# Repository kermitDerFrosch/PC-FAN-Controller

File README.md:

# PC Lüfter Steuerung für 6 PWM 4-Pin Lüfter
(incl. Gerber- und Bestückungsdateien)

Der I²C und der UART Port können für die Vernetzung mehrerer Controller oder für Sensoren benutzt werden.

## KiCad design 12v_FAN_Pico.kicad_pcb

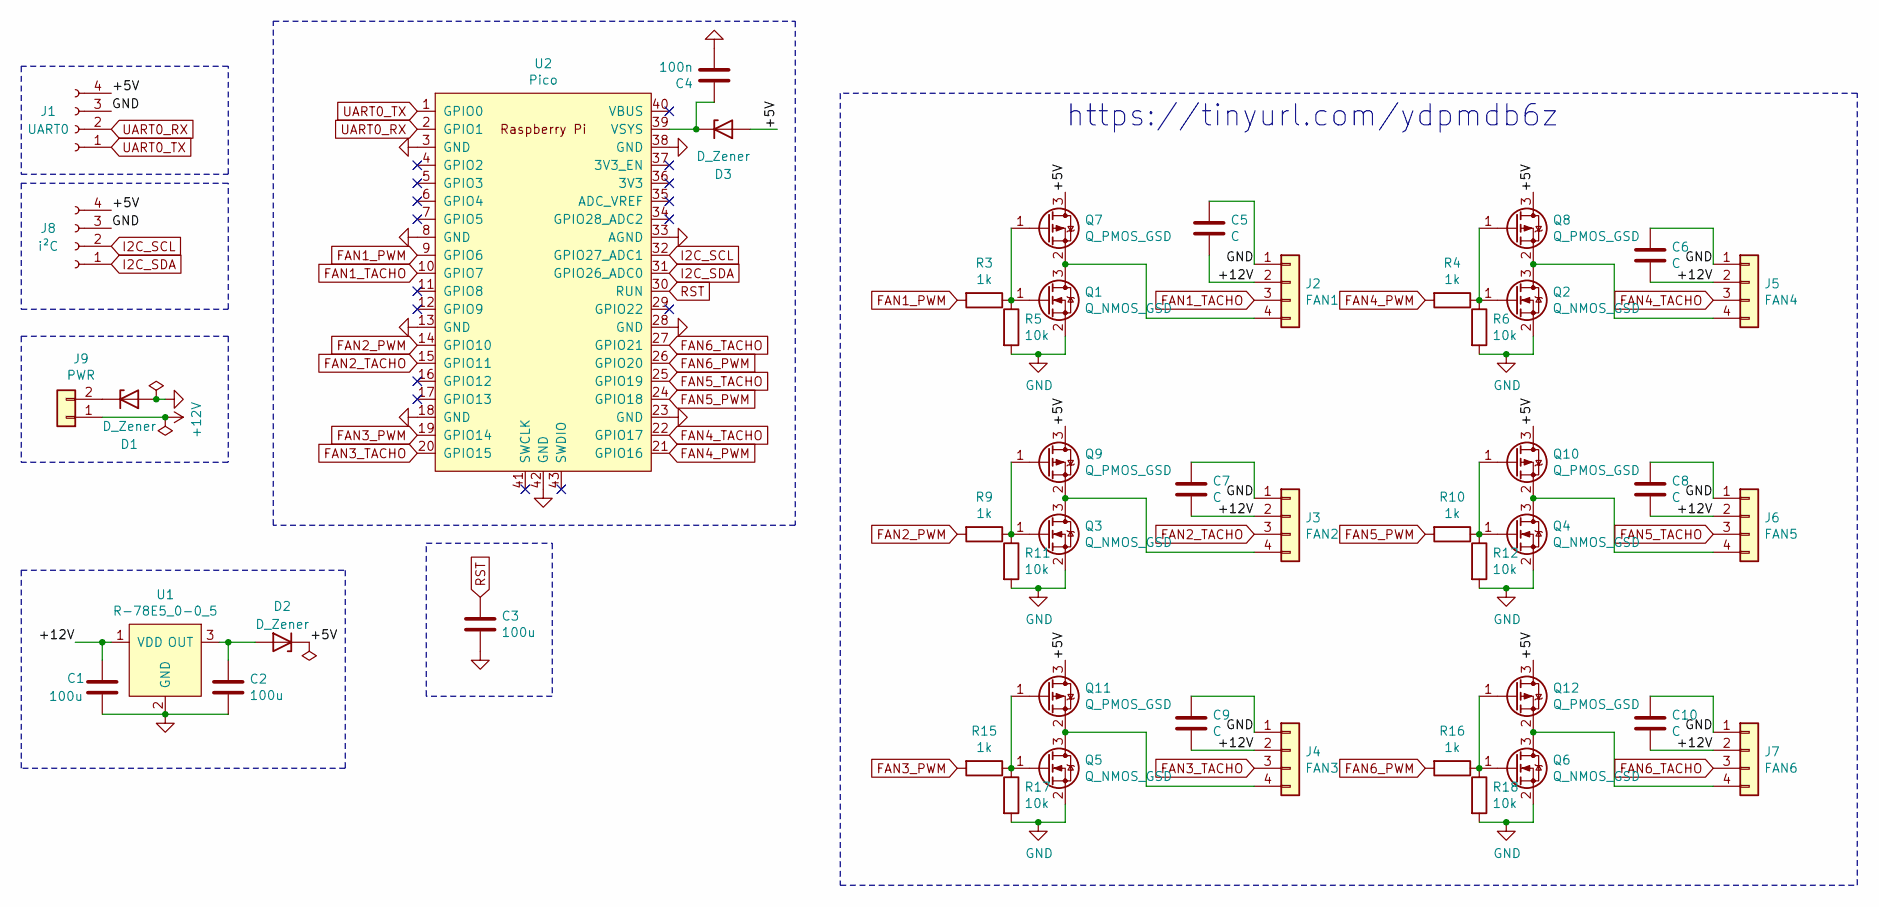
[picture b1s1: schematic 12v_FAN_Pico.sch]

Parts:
C1: 100u; CP_Radial_D6.3mm_P2.50mm
C2, C3: 100u; CP_EIA-3528-21_Kemet-B
C4: 100n; C_0402_1005Metric
C5, C6, C7, C8, C9, C10: C; C_0603_1608Metric
D1, D2, D3: D_Zener; D_A-405_P2.54mm_Vertical_AnodeUp
J1: UART0; NS-Tech_Grove_1x04_P2mm_Vertical
J2: FAN1; FanPinHeader_1x04_P2.54mm_Vertical
J3: FAN2; FanPinHeader_1x04_P2.54mm_Vertical
J4: FAN3; FanPinHeader_1x04_P2.54mm_Vertical
J5: FAN4; FanPinHeader_1x04_P2.54mm_Vertical
J6: FAN5; FanPinHeader_1x04_P2.54mm_Vertical
J7: FAN6; FanPinHeader_1x04_P2.54mm_Vertical
J8: i²C; NS-Tech_Grove_1x04_P2mm_Vertical
J9: PWR; Barrel_Jack_5.5mmODx2.1mmID_PJ-202A
Q1, Q2, Q3, Q4, Q5, Q6: Q_NMOS_GSD; SOT-23
Q7, Q8, Q9, Q10, Q11, Q12: Q_PMOS_GSD; SOT-23
R3, R4, R9, R10, R15, R16: 1k; R_0603_1608Metric
R5, R6, R11, R12, R17, R18: 10k; R_0603_1608Metric
U1: R-78E5_0-0_5; SIP-3_P2.54mm; MPN R-78E5.0-0.5; Digi-Key_PN 945-1648-5-ND
U2: Pico; RPi_Pico_SMD_TH

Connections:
+12V: C1.1, C5.2, C6.2, C7.2, C8.2, C9.2, C10.2, J2.2, J3.2, J4.2, J5.2, J6.2, J7.2, J9.1, U1.1 (VDD)
/+5V: D2.1 (K), D3.2 (A), J1.4, J8.4, Q7.3 (D), Q8.3 (D), Q9.3 (D), Q10.3 (D), Q11.3 (D), Q12.3 (D)
FAN1_PWM: R3.2, U2.9 (GPIO6)
FAN1_TACHO: J2.3, U2.10 (GPIO7)
FAN2_PWM: R9.2, U2.14 (GPIO10)
FAN2_TACHO: J3.3, U2.15 (GPIO11)
FAN3_PWM: R15.2, U2.19 (GPIO14)
FAN3_TACHO: J4.3, U2.20 (GPIO15)
FAN4_PWM: R4.2, U2.21 (GPIO16)
FAN4_TACHO: J5.3, U2.22 (GPIO17)
FAN5_PWM: R10.2, U2.24 (GPIO18)
FAN5_TACHO: J6.3, U2.25 (GPIO19)
FAN6_PWM: R16.2, U2.26 (GPIO20)
FAN6_TACHO: J7.3, U2.27 (GPIO21)
GND: C1.2, C2.2, C3.2, C4.2, C5.1, C6.1, C7.1, C8.1, C9.1, C10.1, D1.2 (A), J1.3, J2.1, J3.1, J4.1, J5.1, J6.1, J7.1, J8.3, Q1.2 (S), Q2.2 (S), Q3.2 (S), Q4.2 (S), Q5.2 (S), Q6.2 (S), R5.2, R6.2, R11.2, R12.2, R17.2, R18.2, U1.2 (GND), U2.3 (GND), U2.8 (GND), U2.13 (GND), U2.18 (GND), U2.23 (GND), U2.28 (GND), U2.33 (AGND), U2.38 (GND), U2.42 (GND)
I2C_SCL: J8.2, U2.32 (GPIO27_ADC1)
I2C_SDA: J8.1, U2.31 (GPIO26_ADC0)
unnamed: C2.1, D2.2 (A), U1.3 (OUT)
unnamed: C4.1, D3.1 (K), U2.39 (VSYS)
unnamed: D1.1 (K), J9.2
unnamed: J2.4, Q1.3 (D), Q7.2 (S)
unnamed: J3.4, Q3.3 (D), Q9.2 (S)
unnamed: J4.4, Q5.3 (D), Q11.2 (S)
unnamed: J5.4, Q2.3 (D), Q8.2 (S)
unnamed: J6.4, Q4.3 (D), Q10.2 (S)
unnamed: J7.4, Q6.3 (D), Q12.2 (S)
unnamed: Q1.1 (G), Q7.1 (G), R3.1, R5.1
unnamed: Q2.1 (G), Q8.1 (G), R4.1, R6.1
unnamed: Q3.1 (G), Q9.1 (G), R9.1, R11.1
unnamed: Q4.1 (G), Q10.1 (G), R10.1, R12.1
unnamed: Q5.1 (G), Q11.1 (G), R15.1, R17.1
unnamed: Q6.1 (G), Q12.1 (G), R16.1, R18.1
RST: C3.1, U2.30 (RUN)
UART0_RX: J1.2, U2.2 (GPIO1)
UART0_TX: J1.1, U2.1 (GPIO0)

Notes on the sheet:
https://tinyurl.com/ydpmdb6z

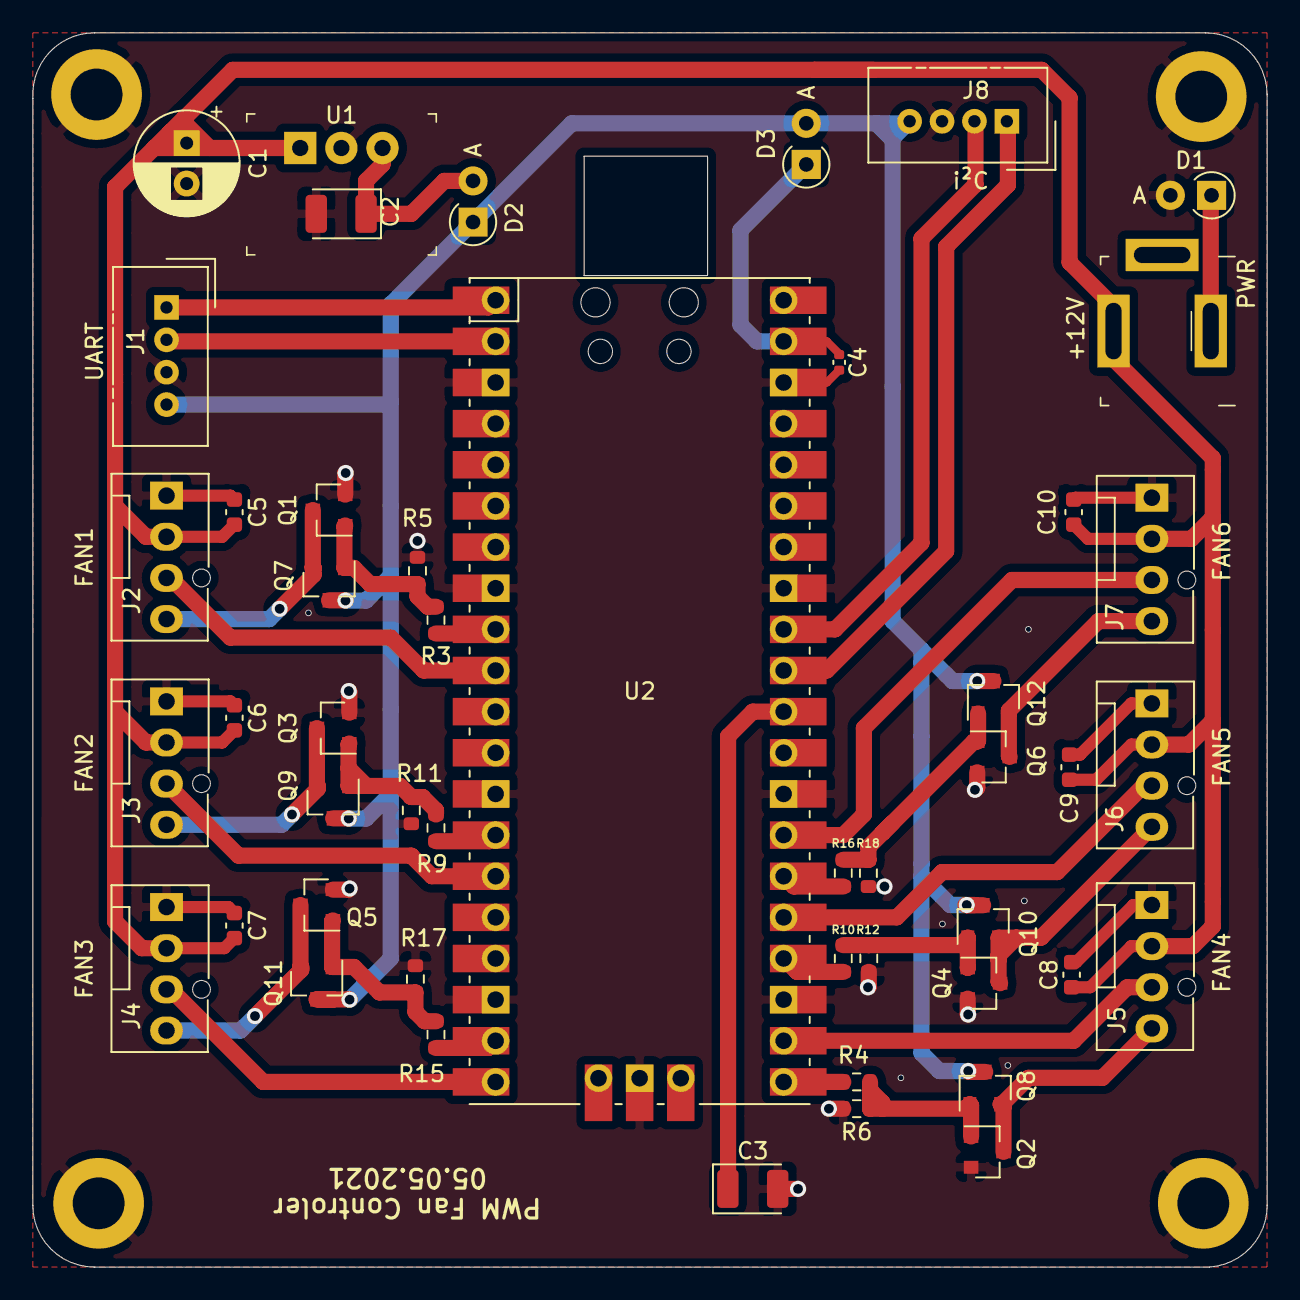
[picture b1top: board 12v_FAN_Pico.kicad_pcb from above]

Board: 2 copper layers, 76.2 x 76.2 mm, 48 parts (0 on the bottom side), 35 nets.

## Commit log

2021-05-17 init incl. gerber and assembly files
2021-05-17 Create LICENSE
